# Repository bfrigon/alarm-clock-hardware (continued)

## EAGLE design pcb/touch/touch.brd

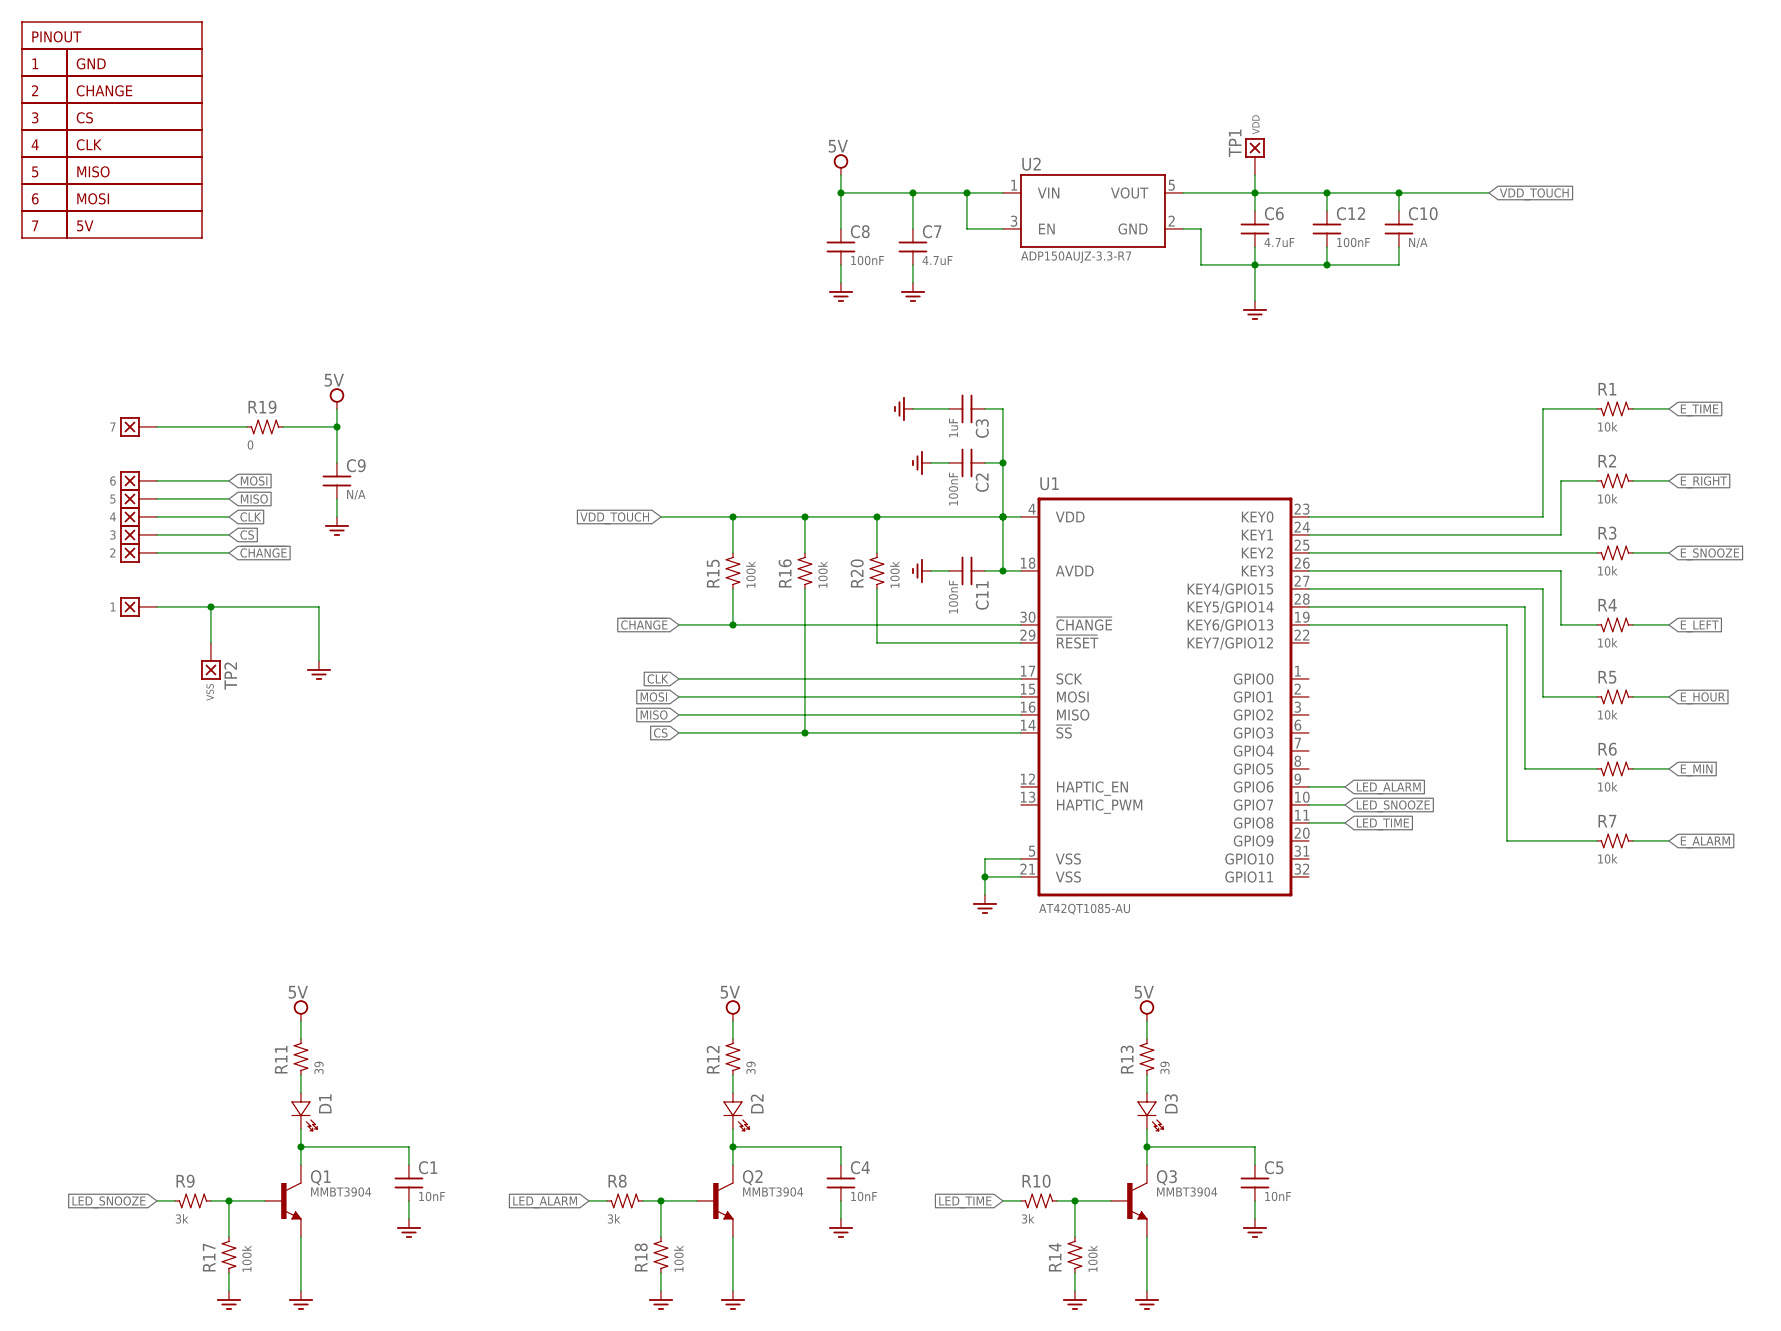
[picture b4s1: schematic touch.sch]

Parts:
5V: 7; WIRE_SMT_150X75
!CHANGE: 2; WIRE_SMT_125X50
C1, C4, C5: 10nF; SMD_0603
C2, C8, C11, C12: 100nF; SMD_0603
C3: 1uF; SMD_1206
C6, C7: 4.7uF; SMD_1206
C9, C10: N/A; SMD_1206
CLK: 4; WIRE_SMT_125X50
CS: 3; WIRE_SMT_125X50
D1, D2, D3: {ATTR:COLOR}; P47F
GND: 1; WIRE_SMT_150X75
MISO: 5; WIRE_SMT_125X50
MOSI: 6; WIRE_SMT_125X50
Q1, Q2, Q3: MMBT3904; SOT23
R1, R2, R3, R4, R5, R6, R7: 10k; SMD_0603
R8, R9, R10: 3k; SMD_0603
R11, R12, R13: 39; SMD_0603
R14, R15, R16, R17, R18, R20: 100k; SMD_0603
R19: 0; SMD_1206
TP1: VDD; TP_050
TP2: VSS; TP_050
U1: AT42QT1085-AU; TQFP-7X7-32
U2: ADP150AUJZ-3.3-R7; SOT23-5

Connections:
5V: C7.1, C8.1, C9.1, R11.2, R12.2, R13.2, R19.2, U2.1 (VIN), U2.3 (EN)
!CHANGE: !CHANGE.1, R15.1, U1.30 (!CHANGE)
CLK: CLK.1, U1.17 (SCK)
CS: CS.1, R16.1, U1.14 (!SS)
E_ALARM: R7.2
E_HOUR: R5.2
E_LEFT: R4.2
E_MIN: R6.2
E_RIGHT: R2.2
E_SNOOZE: R3.2
E_TIME: R1.2
GND: C1.2, C2.2, C3.2, C4.2, C5.2, C6.2, C7.2, C8.2, C9.2, C10.2, C11.2, C12.2, GND.1, Q1.2 (E), Q2.2 (E), Q3.2 (E), R14.1, R17.1, R18.1, TP2.1, U1.5 (VSS), U1.21 (VSS), U2.2 (GND)
LED_ALARM: R8.1, U1.9 (GPIO6)
LED_SNOOZE: R9.1, U1.10 (GPIO7)
LED_TIME: R10.1, U1.11 (GPIO8)
MISO: MISO.1, U1.16 (MISO)
MOSI: MOSI.1, U1.15 (MOSI)
unnamed: C1.1, D1.K, Q1.3 (C)
unnamed: C4.1, D2.K, Q2.3 (C)
unnamed: C5.1, D3.K, Q3.3 (C)
unnamed: D1.A, R11.1
unnamed: D2.A, R12.1
unnamed: D3.A, R13.1
unnamed: R1.1, U1.23 (KEY0)
unnamed: R2.1, U1.24 (KEY1)
unnamed: R3.1, U1.25 (KEY2)
unnamed: R4.1, U1.26 (KEY3)
unnamed: R5.1, U1.27 (KEY4/GPIO15)
unnamed: R6.1, U1.28 (KEY5/GPIO14)
unnamed: R7.1, U1.19 (KEY6/GPIO13)
unnamed: Q3.1 (B), R10.2, R14.2
unnamed: Q2.1 (B), R8.2, R18.2
unnamed: Q1.1 (B), R9.2, R17.2
unnamed: 5V.1, R19.1
unnamed: R20.1, U1.29 (!RESET)
VDD_TOUCH: C2.1, C3.1, C6.1, C10.1, C11.1, C12.1, R15.2, R16.2, R20.2, TP1.1, U1.4 (VDD), U1.18 (AVDD), U2.5 (VOUT)

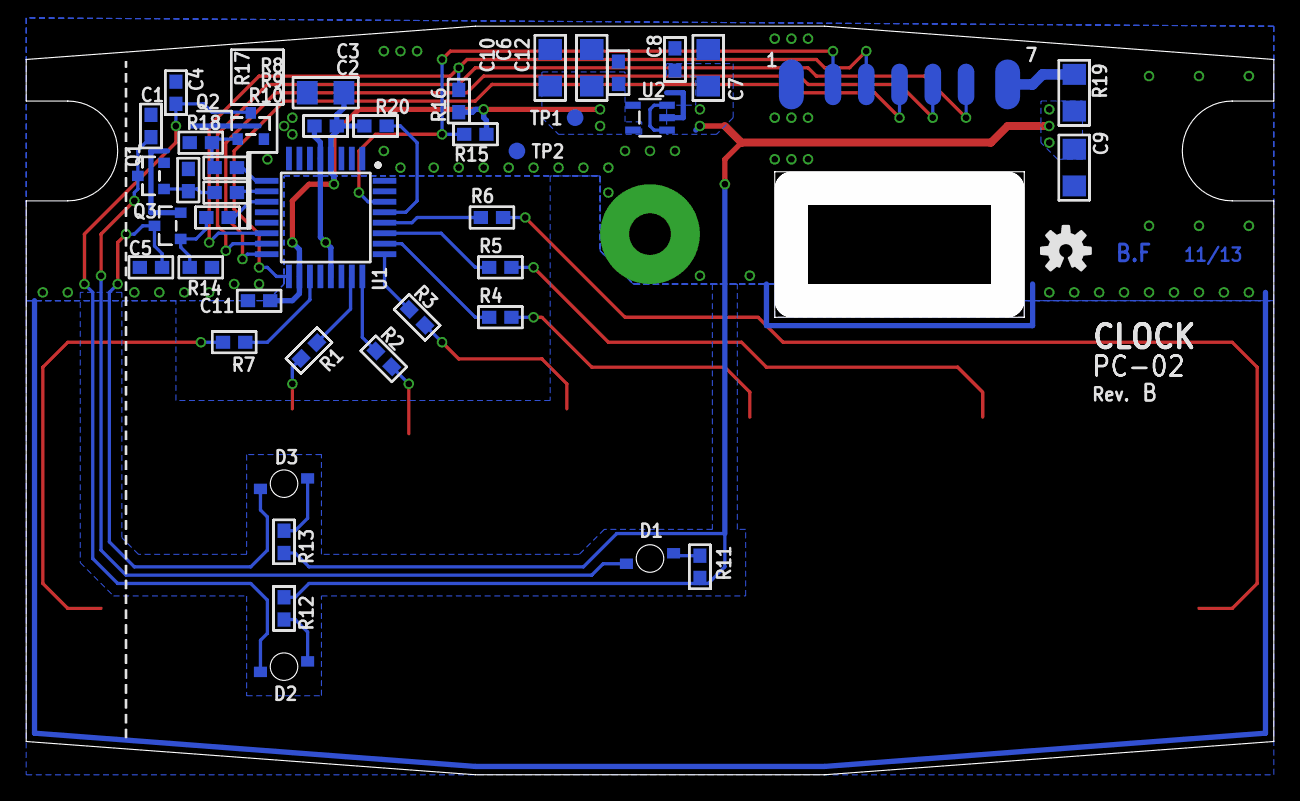
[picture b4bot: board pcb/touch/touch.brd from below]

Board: 2 copper layers, 95.2 x 57.1 mm, 51 parts (51 on the bottom side), 29 nets.

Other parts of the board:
U$3: INFO_COMPACT
U$5: OPENHW_LOGO_150

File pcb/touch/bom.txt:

**********************************************************************************
*                                BILL OF MATERIAL                                *
**********************************************************************************

Last mod. : 2014-12-29 01:49:55
Doc. ID   : CLK-SCH-02
Project   : Alarm Clock
Title     : Touch keypad
             
Part #    : CLK-PC-02
REV.      : B


Qty | Names              | Description                    | Mfg. SKU        | Package      | Value     
=======================================================================================================
  1 | U2                 | Ultralow Noise, 150 mA CMOS    | ADP150AUJZ-3.3- | SOT23-5      | --        
    |                    | Linear Regulator - 3.3v        | R7              |              |           
----|--------------------|--------------------------------|-----------------|--------------|-----------
  1 | U1                 | 8 Key QTouch touch sensor      | AT42QT1085-AU   | TQFP-7X7-32  | --        
----|--------------------|--------------------------------|-----------------|--------------|-----------
  4 | C2, C8, C11-C12    | Capacitor - SMT 0603 - 100nF   | CAP-0603        | SMT 0603     | 100nF     
----|--------------------|--------------------------------|-----------------|--------------|-----------
  3 | C1, C4-C5          | Capacitor - SMT 0603 - 10nF    | CAP-0603        | SMT 0603     | 10nF      
----|--------------------|--------------------------------|-----------------|--------------|-----------
  1 | C3                 | Capacitor - SMT 1206 - 1uF     | CAP-1206        | SMT 1206     | 1uF       
----|--------------------|--------------------------------|-----------------|--------------|-----------
  2 | C6-C7              | Capacitor - SMT 1206 - 4.7uF   | CAP-1206        | SMT 1206     | 4.7uF     
----|--------------------|--------------------------------|-----------------|--------------|-----------
  3 | D1-D3              | SMT LED 2mm - Bottom entry -   | LR-P47F         | P47F         | --        
    |                    | Red                            |                 |              |           
----|--------------------|--------------------------------|-----------------|--------------|-----------
  3 | Q1-Q3              | NPN Transistor                 | MMBT3904        | SOT23        | --        
----|--------------------|--------------------------------|-----------------|--------------|-----------
  6 | R14-R18, R20       | Resistor - SMT 0603 - 100k     | RES-0603        | SMT 0603     | 100k      
----|--------------------|--------------------------------|-----------------|--------------|-----------
  7 | R1-R7              | Resistor - SMT 0603 - 10k      | RES-0603        | SMT 0603     | 10k       
----|--------------------|--------------------------------|-----------------|--------------|-----------
  3 | R11-R13            | Resistor - SMT 0603 - 39       | RES-0603        | SMT 0603     | 39        
----|--------------------|--------------------------------|-----------------|--------------|-----------
  3 | R8-R10             | Resistor - SMT 0603 - 3k       | RES-0603        | SMT 0603     | 3k        
----|--------------------|--------------------------------|-----------------|--------------|-----------
  1 | R19                | Resistor - SMT 1206 - 0        | RES-1206        | SMT 1206     | 0         
----|--------------------|--------------------------------|-----------------|--------------|-----------

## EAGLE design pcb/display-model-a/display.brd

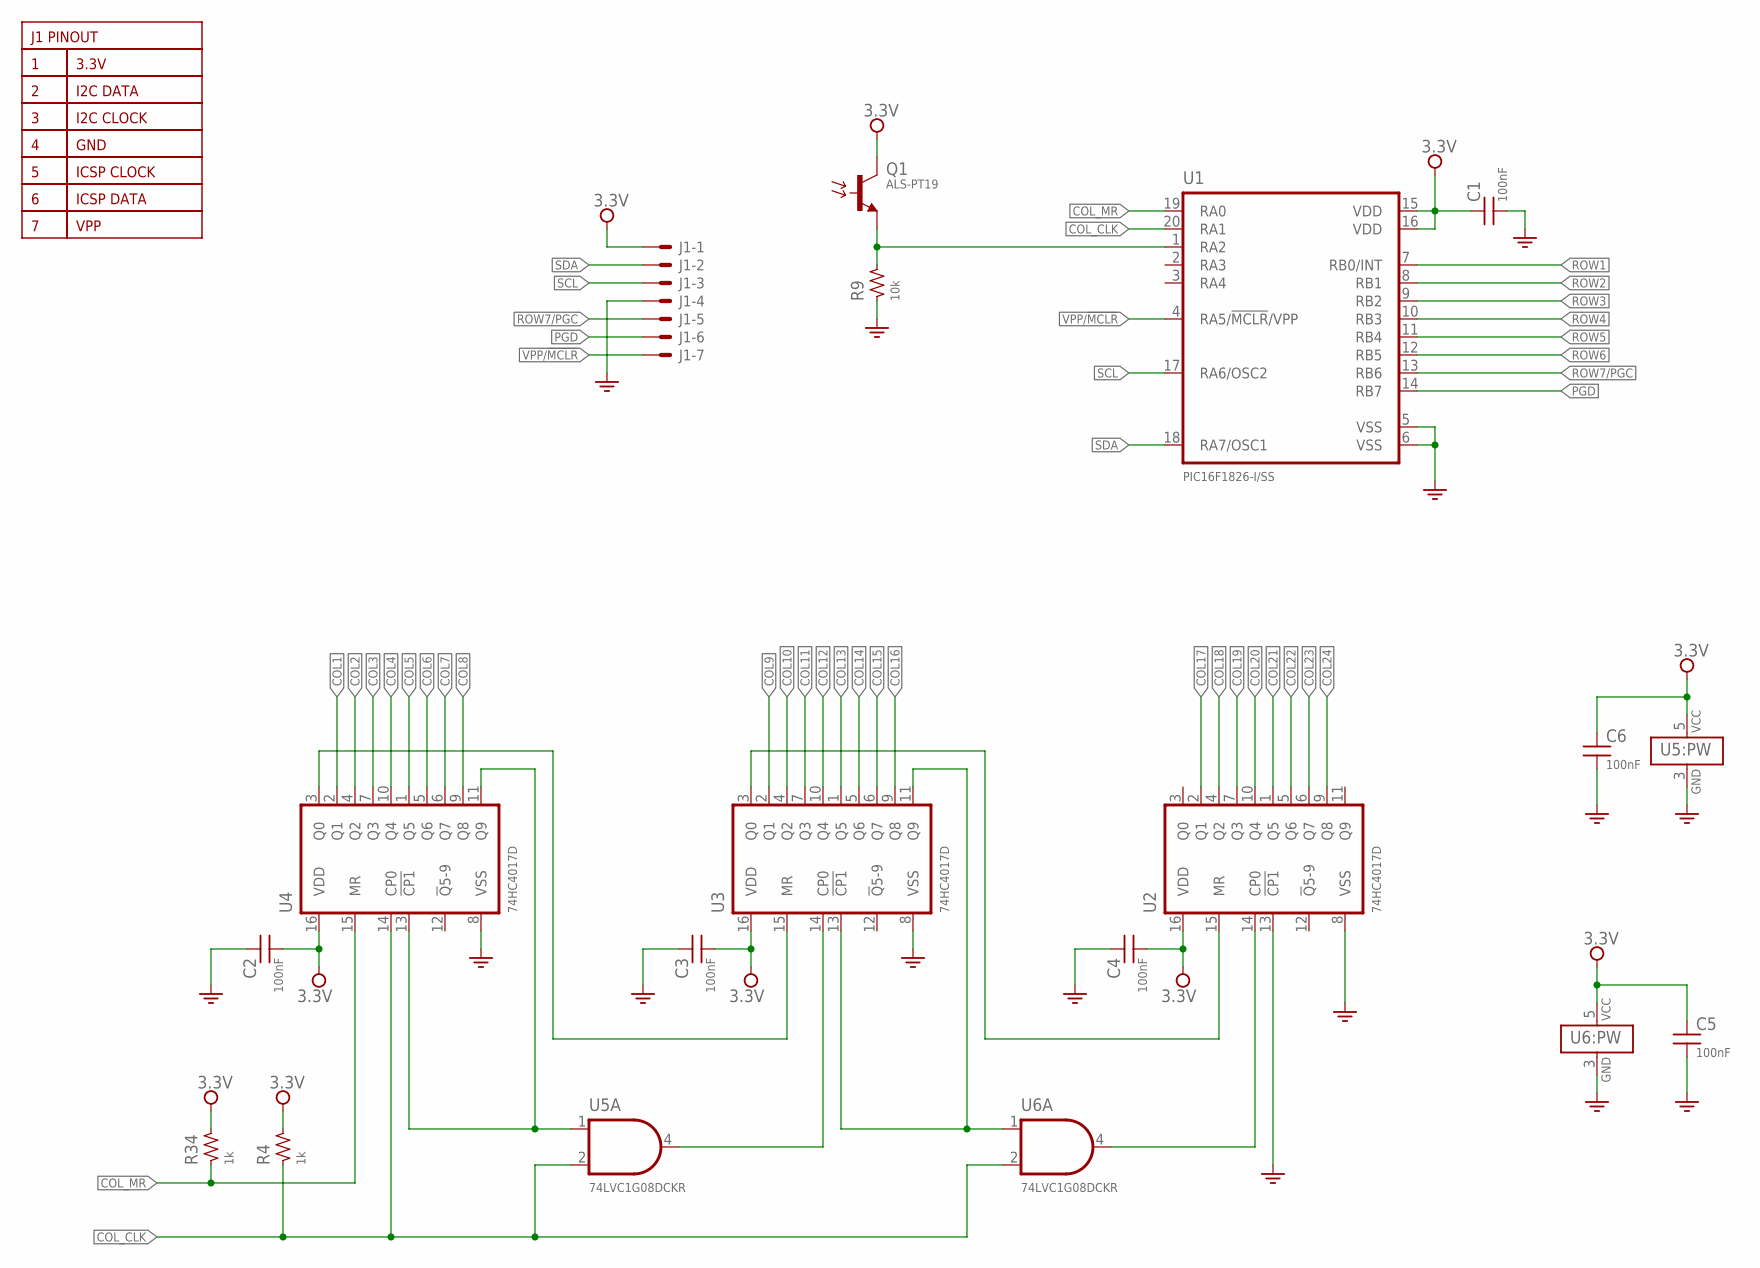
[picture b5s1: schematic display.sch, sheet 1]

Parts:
C1, C2, C3, C4, C5, C6: 100nF; SMD_0603
J1: SNG-2MM-HEADER-07-V; DF3X-7P-2DSA; PART_NO DF3A-7P-2DSA
Q1: ALS-PT19; PART_NO ALS-PT19-315C/L177/TR8
R4, R34: 1k; SMD_0603
R9: 10k; SMD_0603
U1: PIC16F1826-I/SS; SSOP20
U2, U3, U4: 74HC4017D; SOIC16N; PART_NO 74HC4017D,653
U5, U6: 74LVC1G08DCKR; SC70-5

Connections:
3.3V: C1.1, C2.2, C3.2, C4.2, C5.1, C6.1, J1.1, Q1.C, R4.2, R34.2, U1.15 (VDD), U1.16 (VDD), U2.16 (VDD), U3.16 (VDD), U4.16 (VDD), U5.5 (VCC), U6.5 (VCC)
COL1: U4.2 (Q1); also elsewhere on the board
COL2: U4.4 (Q2); also elsewhere on the board
COL3: U4.7 (Q3); also elsewhere on the board
COL4: U4.10 (Q4); also elsewhere on the board
COL5: U4.1 (Q5); also elsewhere on the board
COL6: U4.5 (Q6); also elsewhere on the board
COL7: U4.6 (Q7); also elsewhere on the board
COL8: U4.9 (Q8); also elsewhere on the board
COL9: U3.2 (Q1); also elsewhere on the board
COL10: U3.4 (Q2); also elsewhere on the board
COL11: U3.7 (Q3); also elsewhere on the board
COL12: U3.10 (Q4); also elsewhere on the board
COL13: U3.1 (Q5); also elsewhere on the board
COL14: U3.5 (Q6); also elsewhere on the board
COL15: U3.6 (Q7); also elsewhere on the board
COL16: U3.9 (Q8); also elsewhere on the board
COL17: U2.2 (Q1); also elsewhere on the board
COL18: U2.4 (Q2); also elsewhere on the board
COL19: U2.7 (Q3); also elsewhere on the board
COL20: U2.10 (Q4); also elsewhere on the board
COL21: U2.1 (Q5); also elsewhere on the board
COL22: U2.5 (Q6); also elsewhere on the board
COL23: U2.6 (Q7); also elsewhere on the board
COL24: U2.9 (Q8); also elsewhere on the board
COL_CLK: R4.1, U1.20 (RA1), U4.14 (CP0), U5.2 (I1), U6.2 (I1)
COL_MR: R34.1, U1.19 (RA0), U4.15 (MR)
GND: C1.2, C2.1, C3.1, C4.1, C5.2, C6.2, J1.4, R9.1, U1.5 (VSS), U1.6 (VSS), U2.8 (VSS), U2.13 (!CP1), U3.8 (VSS), U4.8 (VSS), U5.3 (GND), U6.3 (GND); also elsewhere on the board
unnamed: Q1.E, R9.2, U1.1 (RA2)
unnamed: U4.11 (Q9), U4.13 (!CP1), U5.1 (I0)
unnamed: U3.14 (CP0), U5.4 (O)
unnamed: U3.15 (MR), U4.3 (Q0)
unnamed: U2.15 (MR), U3.3 (Q0)
unnamed: U3.11 (Q9), U3.13 (!CP1), U6.1 (I0)
unnamed: U2.14 (CP0), U6.4 (O)
PGD: J1.6, U1.14 (RB7)
ROW1: U1.7 (RB0/INT); also elsewhere on the board
ROW2: U1.8 (RB1); also elsewhere on the board
ROW3: U1.9 (RB2); also elsewhere on the board
ROW4: U1.10 (RB3); also elsewhere on the board
ROW5: U1.11 (RB4); also elsewhere on the board
ROW6: U1.12 (RB5); also elsewhere on the board
ROW7/PGC: J1.5, U1.13 (RB6); also elsewhere on the board
SCL: J1.3, U1.17 (RA6/OSC2)
SDA: J1.2, U1.18 (RA7/OSC1)
VPP/!MCLR: J1.7, U1.4 (RA5/!MCLR!/VPP)

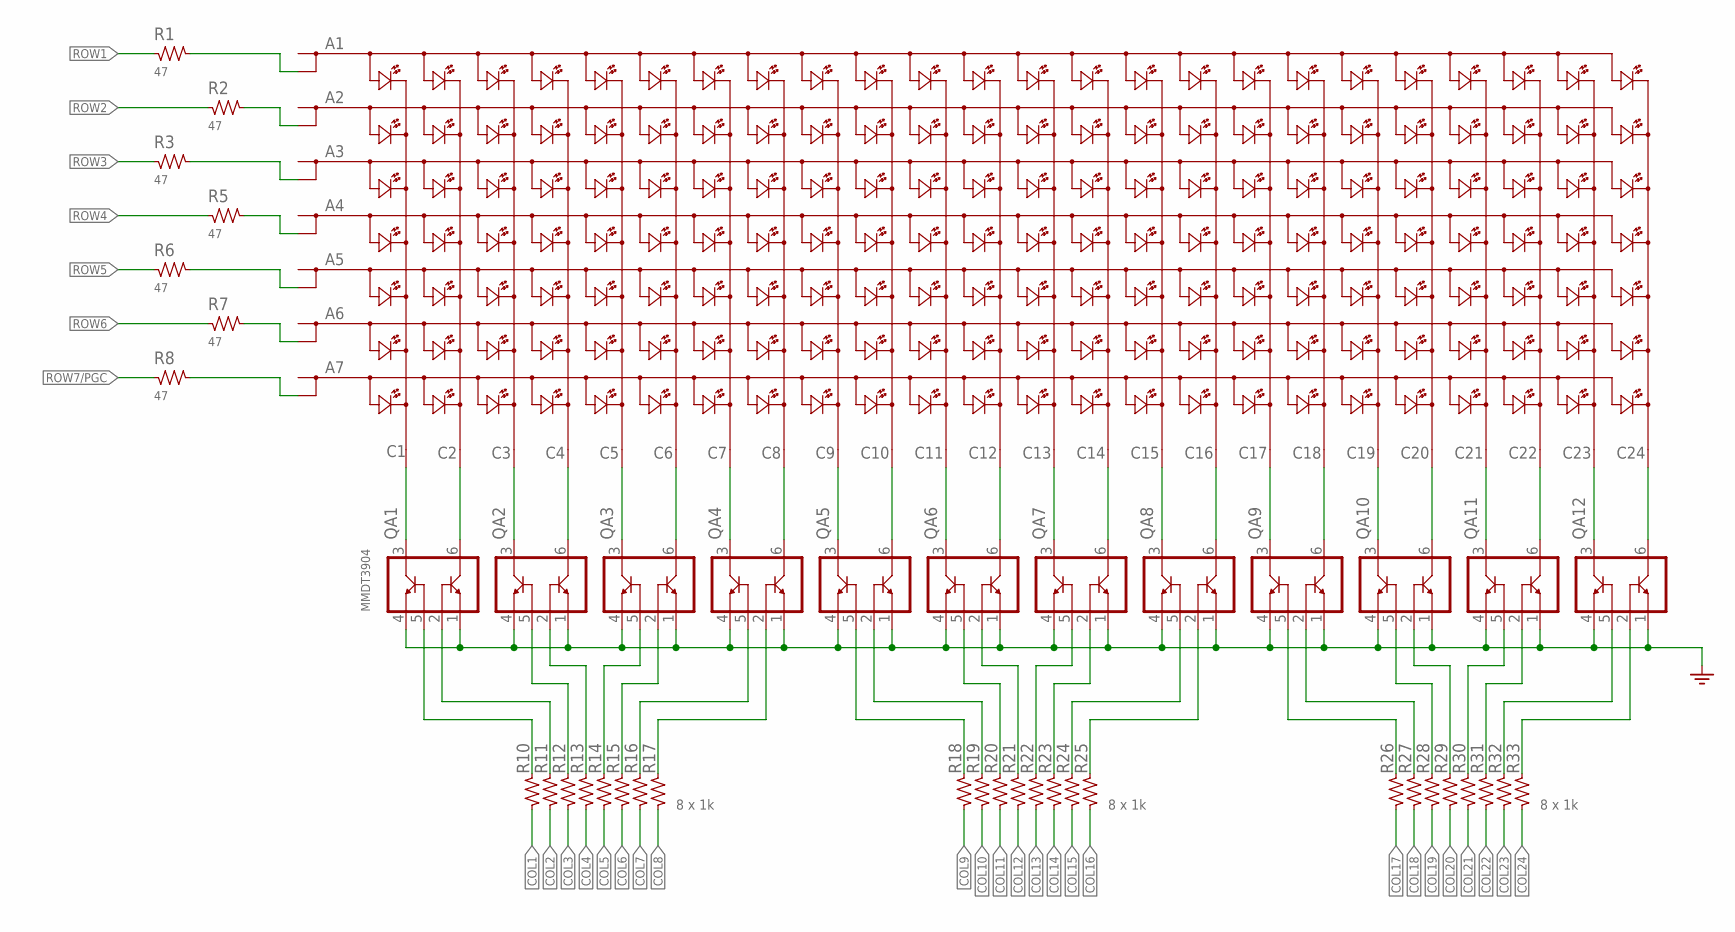
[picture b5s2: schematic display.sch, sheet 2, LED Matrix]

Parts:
QA1, QA2, QA3, QA4, QA5, QA6, QA7, QA8, QA9, QA10, QA11, QA12: MMDT3904; SOT363
R1, R2, R3, R5, R6, R7, R8: 47; SMD_0603
R10, R11, R12, R13, R14, R15, R16, R17, R18, R19, R20, R21, R22, R23, R24, R25, R26, R27, R28, R29, R30, R31, R32, R33: 1k; SMD_0603
U$1: LED_MATRIX_V_24X7

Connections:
COL1: R10.1; also elsewhere on the board
COL2: R11.1; also elsewhere on the board
COL3: R12.1; also elsewhere on the board
COL4: R13.1; also elsewhere on the board
COL5: R14.1; also elsewhere on the board
COL6: R15.1; also elsewhere on the board
COL7: R16.1; also elsewhere on the board
COL8: R17.1; also elsewhere on the board
COL9: R18.1; also elsewhere on the board
COL10: R19.1; also elsewhere on the board
COL11: R20.1; also elsewhere on the board
COL12: R21.1; also elsewhere on the board
COL13: R22.1; also elsewhere on the board
COL14: R23.1; also elsewhere on the board
COL15: R24.1; also elsewhere on the board
COL16: R25.1; also elsewhere on the board
COL17: R26.1; also elsewhere on the board
COL18: R27.1; also elsewhere on the board
COL19: R28.1; also elsewhere on the board
COL20: R29.1; also elsewhere on the board
COL21: R30.1; also elsewhere on the board
COL22: R31.1; also elsewhere on the board
COL23: R32.1; also elsewhere on the board
COL24: R33.1; also elsewhere on the board
GND: QA1.1 (E2), QA1.4 (E1), QA2.1 (E2), QA2.4 (E1), QA3.1 (E2), QA3.4 (E1), QA4.1 (E2), QA4.4 (E1), QA5.1 (E2), QA5.4 (E1), QA6.1 (E2), QA6.4 (E1), QA7.1 (E2), QA7.4 (E1), QA8.1 (E2), QA8.4 (E1), QA9.1 (E2), QA9.4 (E1), QA10.1 (E2), QA10.4 (E1), QA11.1 (E2), QA11.4 (E1), QA12.1 (E2), QA12.4 (E1); also elsewhere on the board
unnamed: R8.2, U$1.A7@2 (A7)
unnamed: R7.2, U$1.A6@2 (A6)
unnamed: R6.2, U$1.A5@2 (A5)
unnamed: R5.2, U$1.A4@2 (A4)
unnamed: R3.2, U$1.A3@2 (A3)
unnamed: R2.2, U$1.A2@2 (A2)
unnamed: R1.2, U$1.A1@2 (A1)
unnamed: QA12.6 (C2), U$1.C24
unnamed: QA12.3 (C1), U$1.C23
unnamed: QA11.6 (C2), U$1.C22
unnamed: QA11.3 (C1), U$1.C21
unnamed: QA10.6 (C2), U$1.C20
unnamed: QA10.3 (C1), U$1.C19
unnamed: QA9.6 (C2), U$1.C18
unnamed: QA9.3 (C1), U$1.C17
unnamed: QA8.6 (C2), U$1.C16
unnamed: QA8.3 (C1), U$1.C15
unnamed: QA7.6 (C2), U$1.C14
unnamed: QA7.3 (C1), U$1.C13
unnamed: QA6.6 (C2), U$1.C12
unnamed: QA6.3 (C1), U$1.C11
unnamed: QA5.6 (C2), U$1.C10
unnamed: QA5.3 (C1), U$1.C9
unnamed: QA4.6 (C2), U$1.C8
unnamed: QA4.3 (C1), U$1.C7
unnamed: QA3.6 (C2), U$1.C6
unnamed: QA3.3 (C1), U$1.C5
unnamed: QA2.6 (C2), U$1.C4
unnamed: QA2.3 (C1), U$1.C3
unnamed: QA1.6 (C2), U$1.C2
unnamed: QA1.3 (C1), U$1.C1
unnamed: QA9.5 (B1), R26.2
unnamed: QA9.2 (B2), R27.2
unnamed: QA10.5 (B1), R28.2
unnamed: QA10.2 (B2), R29.2
unnamed: QA11.5 (B1), R30.2
unnamed: QA11.2 (B2), R31.2
unnamed: QA12.5 (B1), R32.2
unnamed: QA12.2 (B2), R33.2
unnamed: QA8.2 (B2), R25.2
unnamed: QA8.5 (B1), R24.2
unnamed: QA7.2 (B2), R23.2
unnamed: QA7.5 (B1), R22.2
unnamed: QA6.2 (B2), R21.2
unnamed: QA6.5 (B1), R20.2
unnamed: QA5.2 (B2), R19.2
unnamed: QA5.5 (B1), R18.2
unnamed: QA4.2 (B2), R17.2
unnamed: QA4.5 (B1), R16.2
unnamed: QA3.2 (B2), R15.2
unnamed: QA3.5 (B1), R14.2
unnamed: QA2.2 (B2), R13.2
unnamed: QA2.5 (B1), R12.2
unnamed: QA1.2 (B2), R11.2
unnamed: QA1.5 (B1), R10.2
ROW1: R1.1; also elsewhere on the board
ROW2: R2.1; also elsewhere on the board
ROW3: R3.1; also elsewhere on the board
ROW4: R5.1; also elsewhere on the board
ROW5: R6.1; also elsewhere on the board
ROW6: R7.1; also elsewhere on the board
ROW7/PGC: R8.1; also elsewhere on the board

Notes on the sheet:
8 x 1k

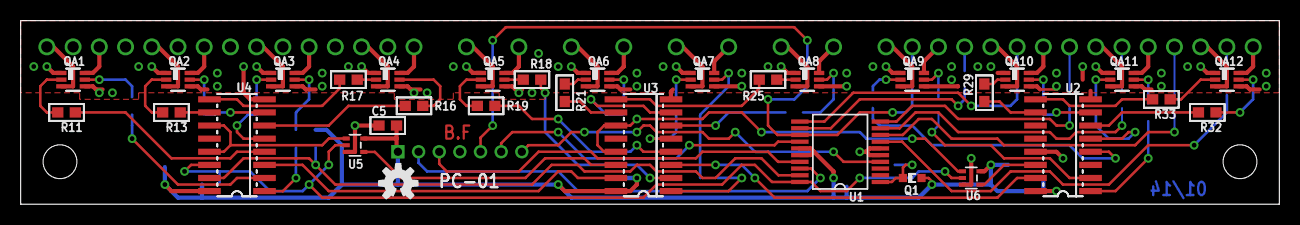
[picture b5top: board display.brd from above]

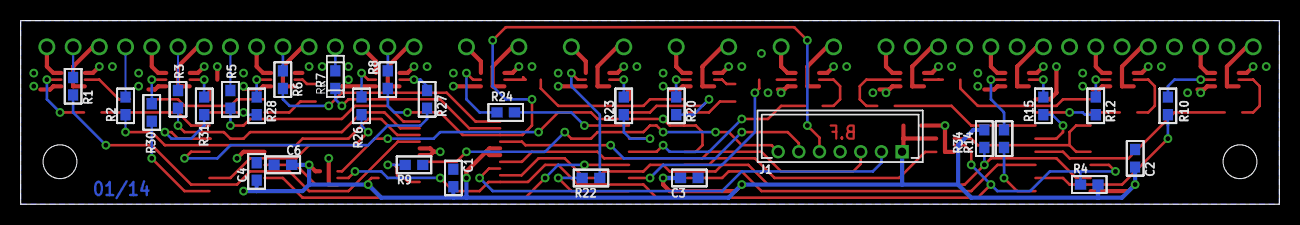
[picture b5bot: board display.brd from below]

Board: 2 copper layers, 121.9 x 17.8 mm, 64 parts (30 on the bottom side), 101 nets.

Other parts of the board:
U$3: OPENHW_LOGO_150
U$6: INFO_DATE
U$7: INFO_AUTHOR

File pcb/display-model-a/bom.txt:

**********************************************************************************
*                                BILL OF MATERIAL                                *
**********************************************************************************

Last mod. : 2014-12-29 01:58:18
Doc. ID   : CLK-SCH-01
Project   : Alarm clock
Title     : LED matrix display board
             
Part #    : CLK-PC-01
REV.      : A


Qty | Names              | Description                    | Mfg. SKU        | Package      | Value     
=======================================================================================================
  3 | U2-U4              | Johnson decade counter         | 74HC4017D,653   | SOIC16N      | --        
----|--------------------|--------------------------------|-----------------|--------------|-----------
  2 | U5-U6              | 2-input AND gate               | 74LVC1G08DCKR   | SC70-5       | --        
----|--------------------|--------------------------------|-----------------|--------------|-----------
  1 | Q1                 | Ambiant light sensor           | ALS-PT19-315C/L | ALS-PT19     | --        
    |                    |                                | 177/TR8         |              |           
----|--------------------|--------------------------------|-----------------|--------------|-----------
  1 | J1                 | 2mm Single Row Header - 7 pos  | DF3A-7P-2DSA    | DF3X-7P-2DSA | --        
    |                    | - SMT Vertical                 |                 |              |           
----|--------------------|--------------------------------|-----------------|--------------|-----------
 12 | QA1-QA12           | NPN transistor - dual          | MMDT3904        | SOT363       | --        
----|--------------------|--------------------------------|-----------------|--------------|-----------
  1 | U1                 | 20 Pin Flash Microcontroller   | PIC16F1826-I/SS | SSOP20       | --        
----|--------------------|--------------------------------|-----------------|--------------|-----------
  6 | C1-C6              | Capacitor - SMT 0603 - 100nF   | --              | SMT 0603     | 100nF     
----|--------------------|--------------------------------|-----------------|--------------|-----------
  1 | R9                 | Resistor - SMT 0603 - 10k      | --              | SMT 0603     | 10k       
----|--------------------|--------------------------------|-----------------|--------------|-----------
 26 | R4, R10-R34        | Resistor - SMT 0603 - 1k       | --              | SMT 0603     | 1k        
----|--------------------|--------------------------------|-----------------|--------------|-----------
  7 | R1-R3, R5-R8       | Resistor - SMT 0603 - 47       | --              | SMT 0603     | 47        
----|--------------------|--------------------------------|-----------------|--------------|-----------

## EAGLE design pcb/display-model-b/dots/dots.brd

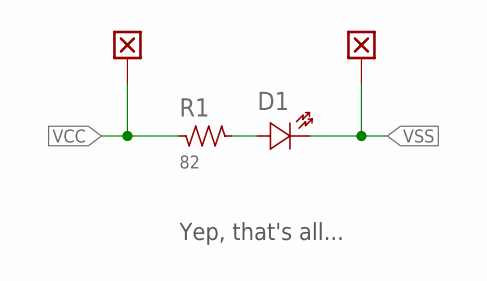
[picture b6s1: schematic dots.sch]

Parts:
D1: {ATTR:COLOR}; CHIPLED_0805; PART_NO APT2012SECK/J4-PRV
R1: 82; SMD_0603
W1, W2: WIRE; WIRE_SMT

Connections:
unnamed: D1.A, R1.2
VCC: R1.1, W1.1
VSS: D1.K, W2.1

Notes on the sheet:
Yep, that's all...

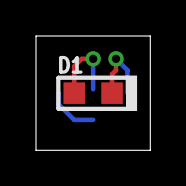
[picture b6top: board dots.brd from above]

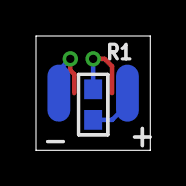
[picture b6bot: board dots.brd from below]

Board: 2 copper layers, 6.3 x 6.3 mm, 4 parts (3 on the bottom side), 3 nets.

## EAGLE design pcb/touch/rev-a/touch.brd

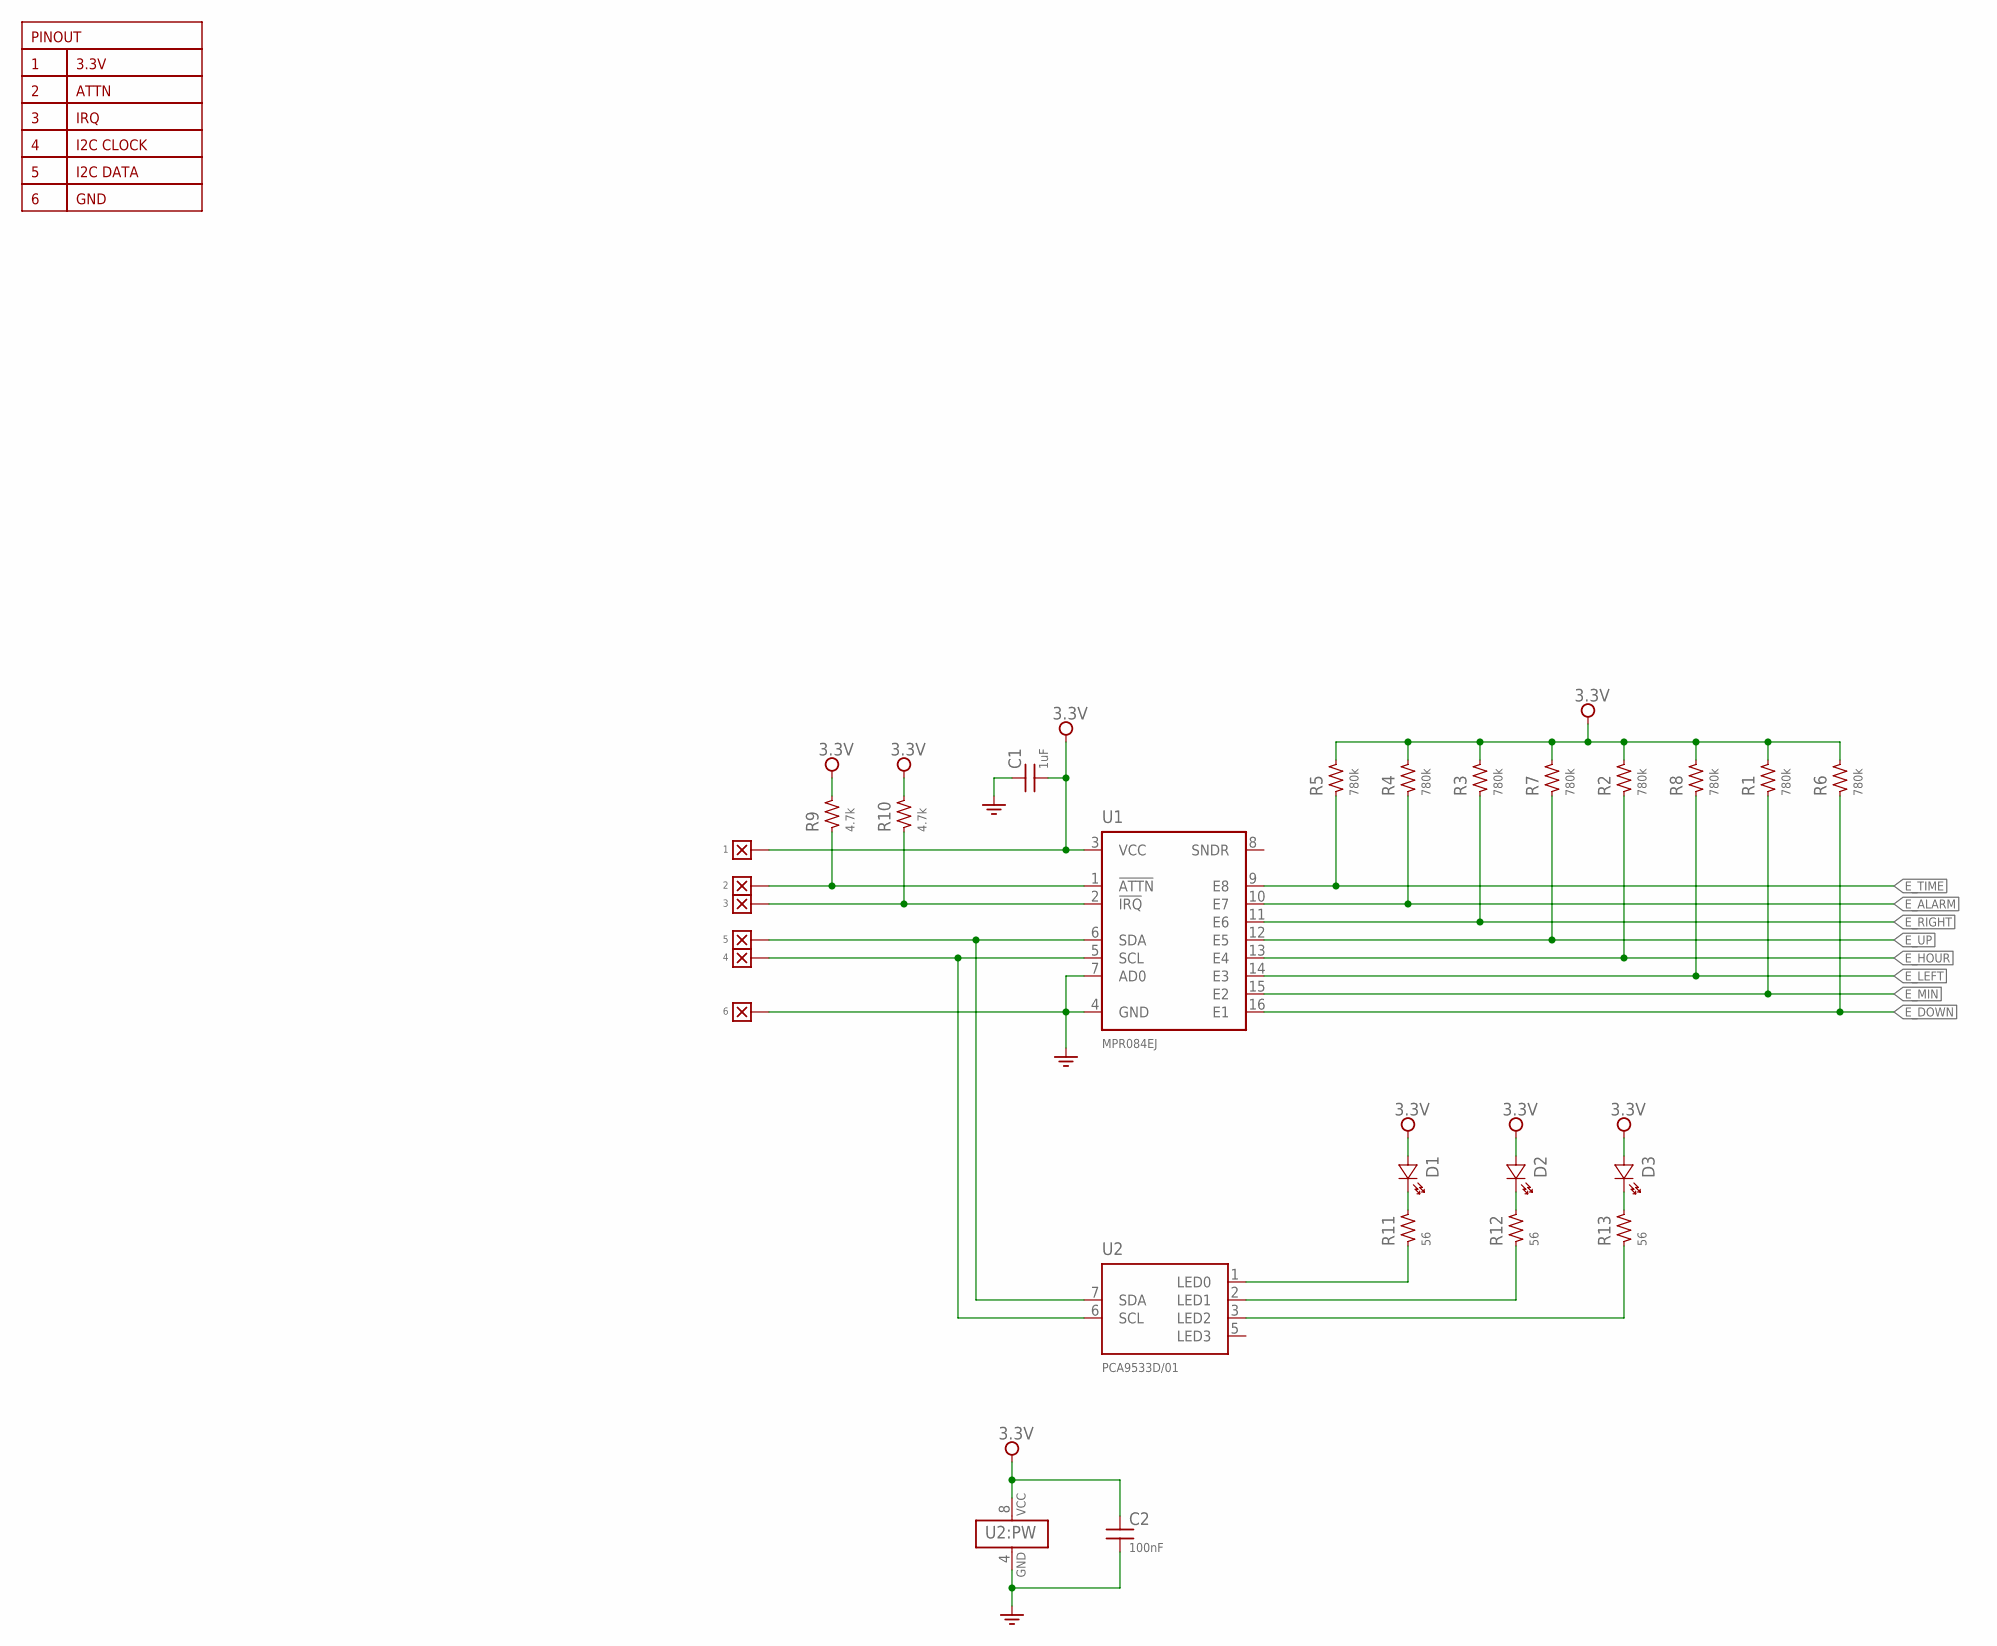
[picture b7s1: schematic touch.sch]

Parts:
3.3V: 1; WIRE_SMT
!ATTN: 2; WIRE_SMT
!IRQ: 3; WIRE_SMT
C1: 1uF; SMD_0603
C2: 100nF; SMD_0603
D1, D2, D3: {ATTR:COLOR}; CHIPLED_0805
R1, R2, R3, R4, R5, R6, R7, R8: 780k; SMD_0603
R9, R10: 4.7k; SMD_0603
R11, R12, R13: 56; SMD_0603
SCL: 4; WIRE_SMT
SDA: 5; WIRE_SMT
U1: MPR084EJ; TSSOP16
U2: PCA9533D/01; SOIC8
W6: 6; WIRE_SMT

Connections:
3.3V: 3.3V.1, C1.2, C2.1, D1.A, D2.A, D3.A, R1.2, R2.2, R3.2, R4.2, R5.2, R6.2, R7.2, R8.2, R9.2, R10.2, U1.3 (VCC), U2.8 (VCC)
!ATTN: !ATTN.1, R9.1, U1.1 (!ATTN)
!IRQ: !IRQ.1, R10.1, U1.2 (!IRQ)
E_ALARM: R4.1, U1.10 (E7)
E_DOWN: R6.1, U1.16 (E1)
E_HOUR: R2.1, U1.13 (E4)
E_LEFT: R8.1, U1.14 (E3)
E_MIN: R1.1, U1.15 (E2)
E_RIGHT: R3.1, U1.11 (E6)
E_TIME: R5.1, U1.9 (E8)
E_UP: R7.1, U1.12 (E5)
GND: C1.1, C2.2, U1.4 (GND), U1.7 (AD0), U2.4 (GND), W6.1
unnamed: D1.K, R11.2
unnamed: D2.K, R12.2
unnamed: D3.K, R13.2
unnamed: R11.1, U2.1 (LED0)
unnamed: R12.1, U2.2 (LED1)
unnamed: R13.1, U2.3 (LED2)
SCL: SCL.1, U1.5 (SCL), U2.6 (SCL)
SDA: SDA.1, U1.6 (SDA), U2.7 (SDA)

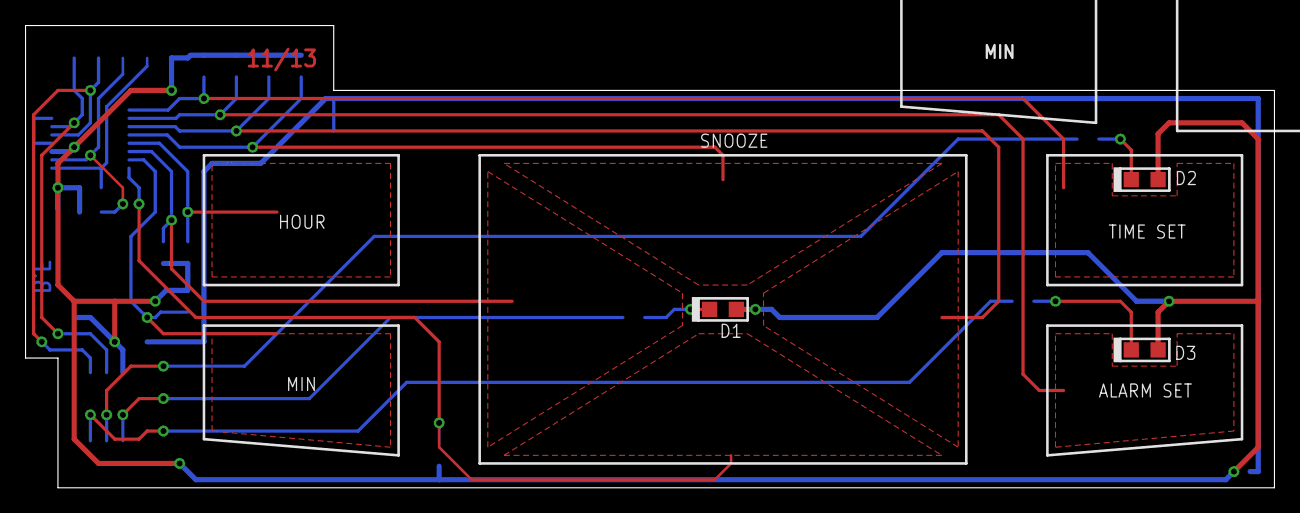
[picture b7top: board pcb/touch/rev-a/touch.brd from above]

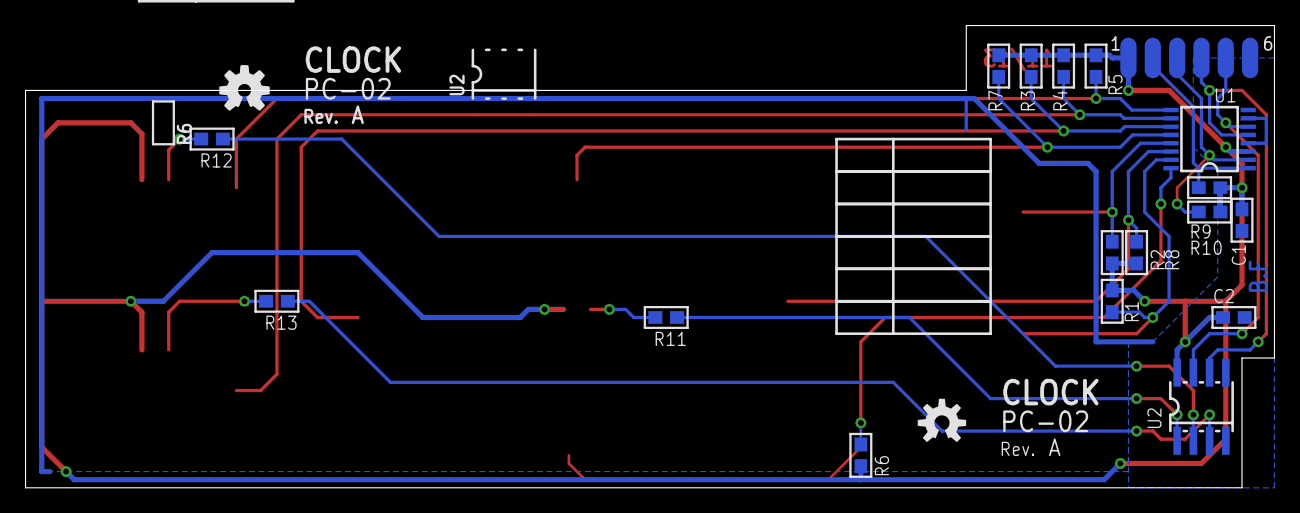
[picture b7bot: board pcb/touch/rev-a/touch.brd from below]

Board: 2 copper layers, 97.8 x 36.2 mm, 36 parts (32 on the bottom side), 20 nets.

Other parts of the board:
U$1: INFO_AUTHOR
U$2: INFO_DATE
U$3: INFO_COMPACT
U$5: OPENHW_LOGO_150
U$11, U$12, U$13, U$14, U$15, U$16: LEGEND_ROW_30
